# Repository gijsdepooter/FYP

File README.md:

# FYP
Developing a Single Channel Ultrasound Device

This project is being done with the Imperial College London Bioengineering Department, in collaboration with Prof Manos Drakakis and PhD Momen Kamal Tageldeen

This is a Repo for all the relevant material that I am developing/using for a low cost US scanner.

There are a few main parts of the US hardware:

1. The Pulser 
2. The MUX
3. The VGA (voltage gain amplifier)
4. The ADC

**PULSER**

The pulser is responsible for sending high voltage pulses to the piezo transducers in the US probe. I am using the HV7361 from microchip. It takes simple 3 bit digital instructions. These controlls are sent from the raspberry pi pico using the PIO interface to achieve precise timings.

**VGA**

The VGA controlls the amplification of the US signal and corrects for an attenuation of approximately 1dB/MHz/cm in tissue. The TGC profile is set by the MCP4921 DAC, controlled over SPI.
This is a 12 bit DAC that is controlled using the PIO interface of the rapsberry pi pico to achieve the desired speed.

**ADC** 

This project uses the LTC2236, a 10 bit DAC that can sample up to 65Msps. The ADC has a parallel output. The raspberry pi zero is used to decode the parallel ouptut using DMA and the secondary memory interface (SMI). Most of the code that controlls the ADC is from https://github.com/jbentham/rpi, and merely adapted to suit the needs of the IC of choice.

**MUX**

The multiplexer unit is an optional IC to leverage the single channel architecture of this board to controll multiple transducer channels. This allows for constructing B-Mode images with linear and phased arrays.

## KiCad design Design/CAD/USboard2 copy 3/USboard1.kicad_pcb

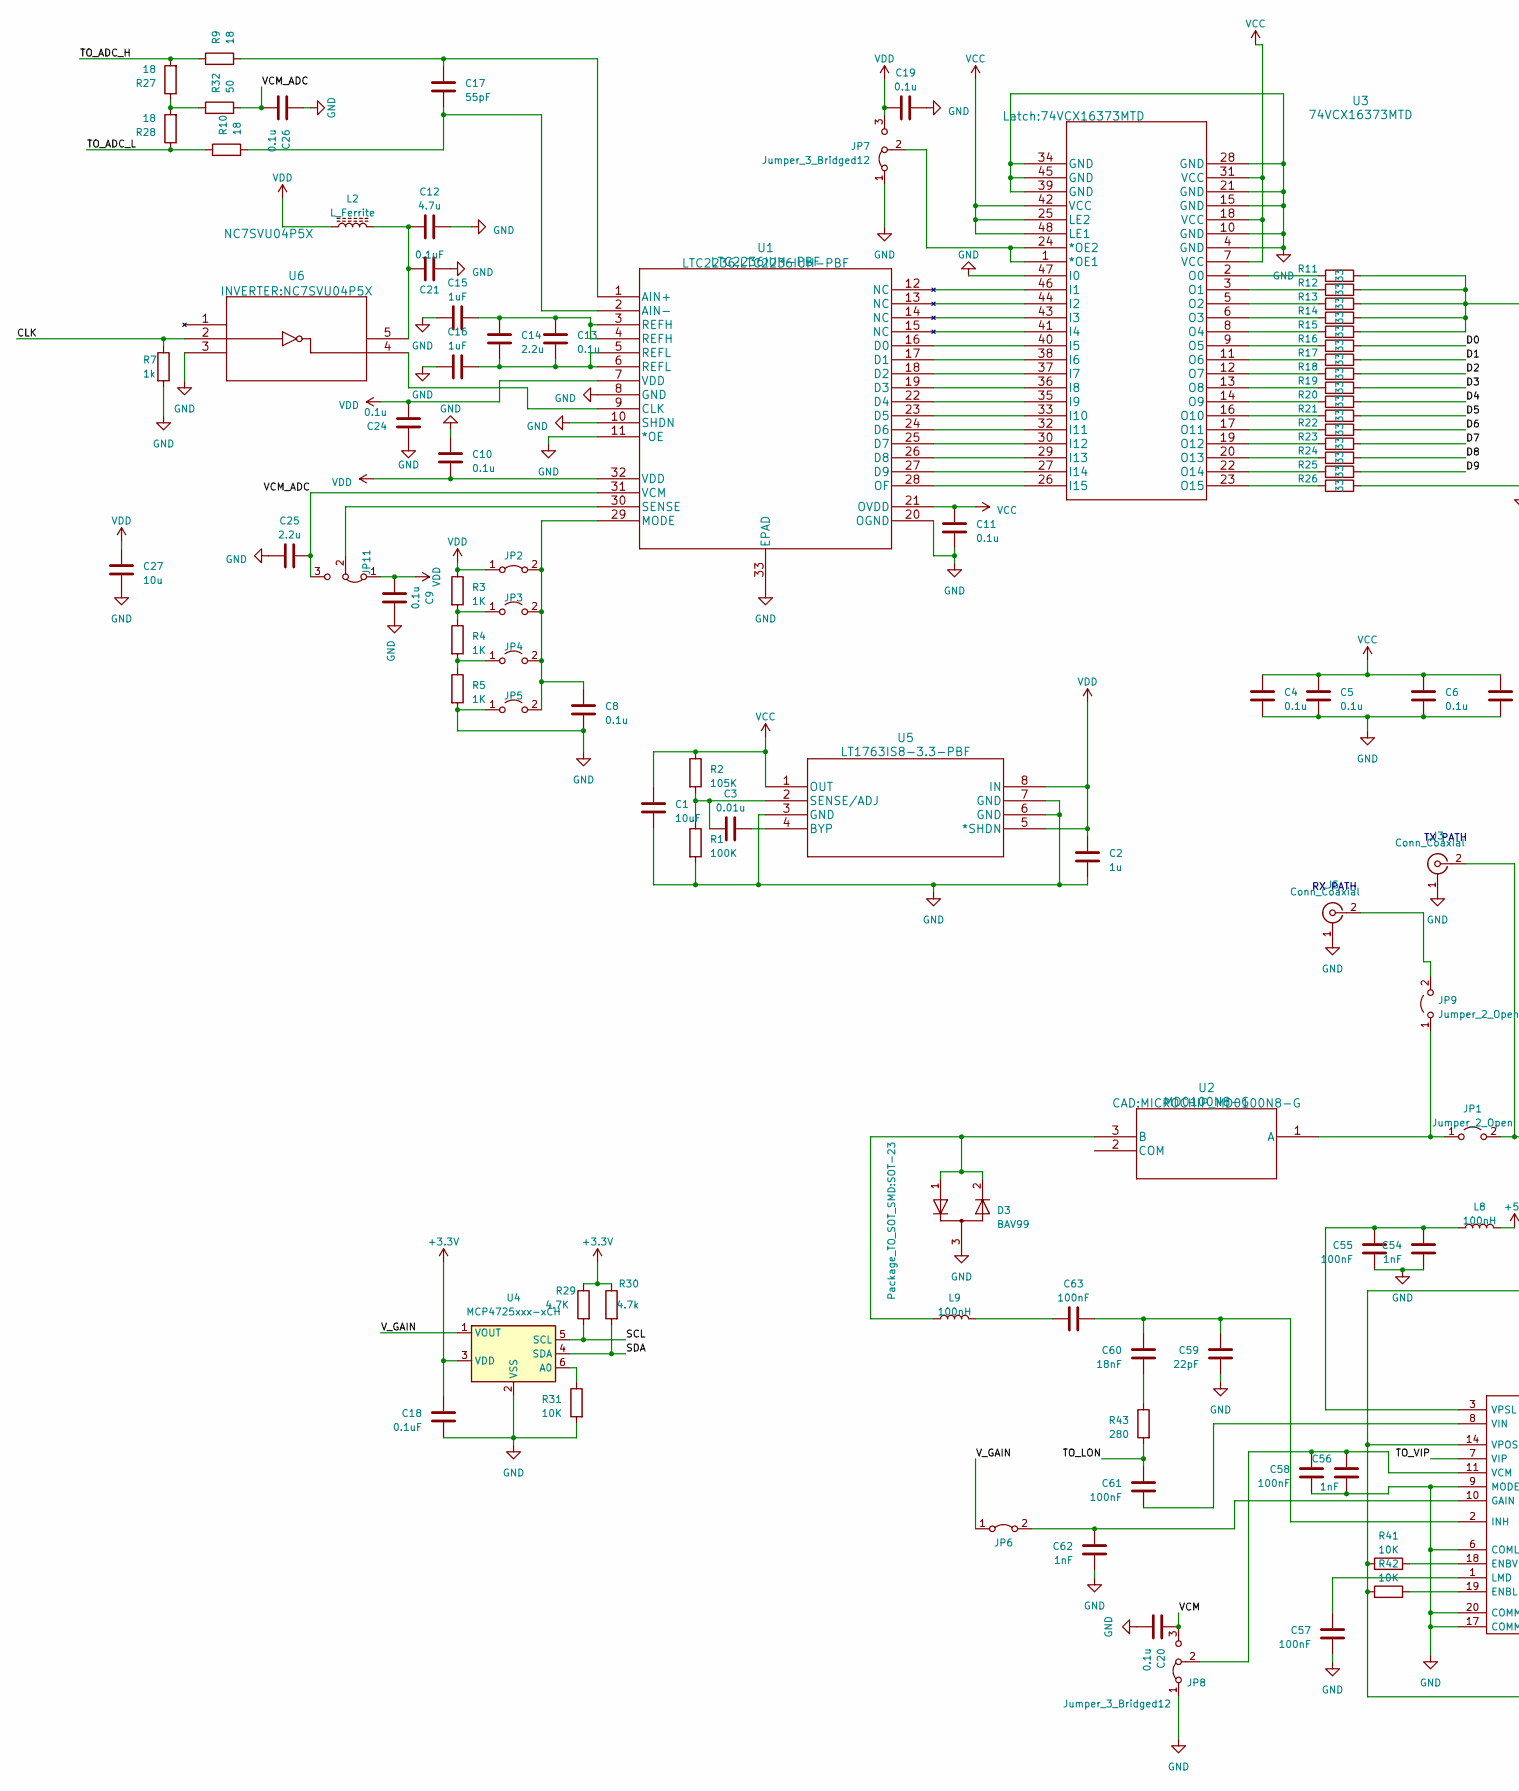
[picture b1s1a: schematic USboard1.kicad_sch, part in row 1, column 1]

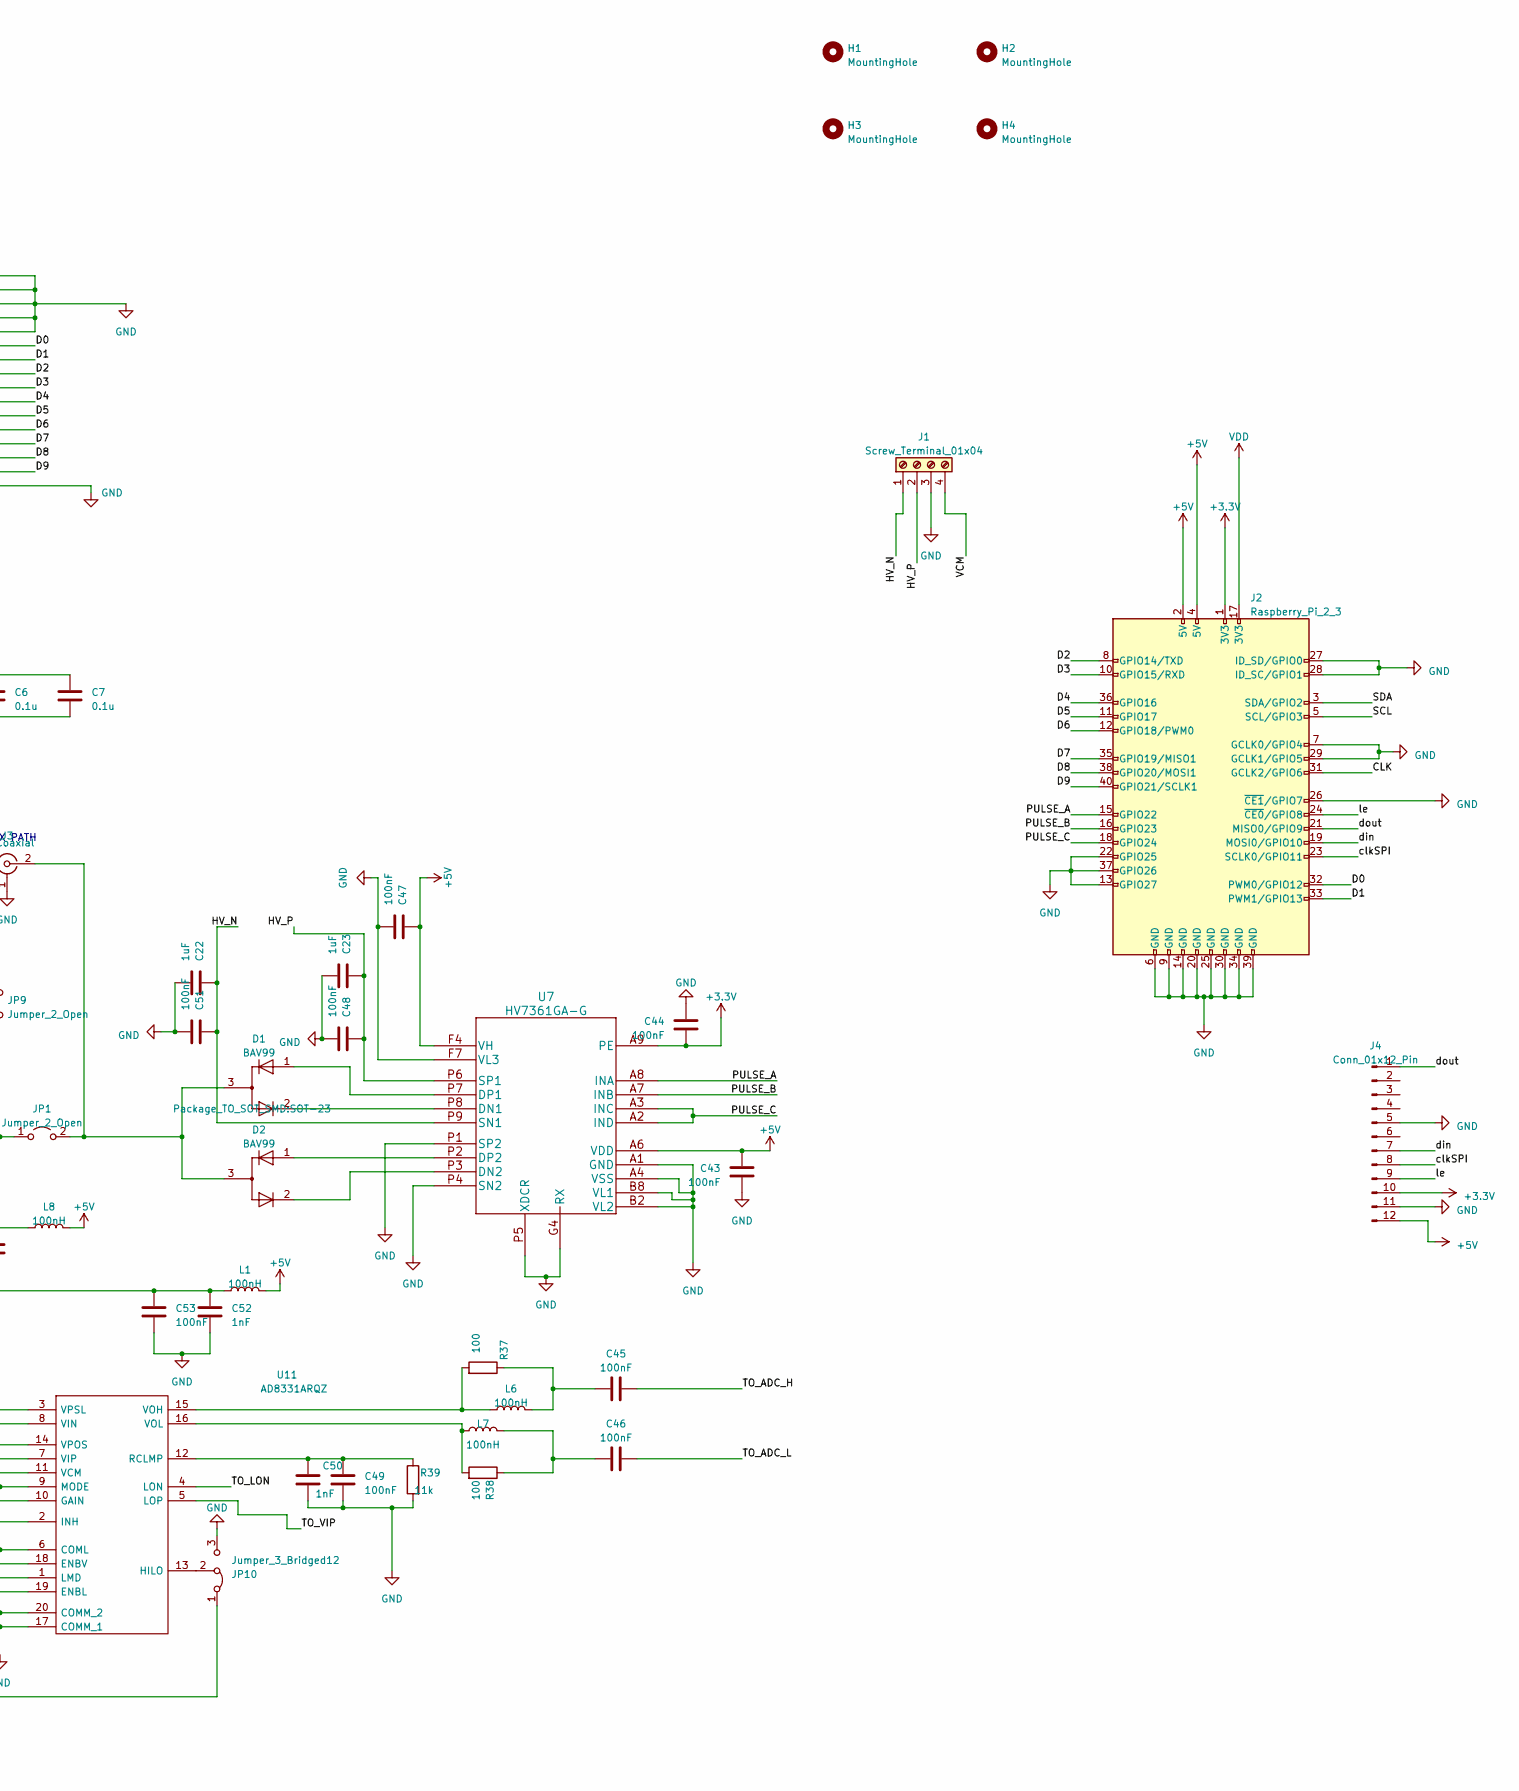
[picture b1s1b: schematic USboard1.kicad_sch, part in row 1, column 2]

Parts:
C1: 10uF; C_0603_1608Metric
C2: 1u; C_0603_1608Metric
C3: 0.01u; C_0603_1608Metric
C4, C5, C6, C7, C8, C9, C10, C11, C13, C19, C20, C24, C26: 0.1u; C_0603_1608Metric
C12: 4.7u; C_0603_1608Metric
C14, C25: 2.2u; C_0603_1608Metric
C15, C16: 1uF; C_0603_1608Metric
C17: 55pF; C_0603_1608Metric
C18, C21: 0.1uF; C_0603_1608Metric
C22, C23: 1uF; C_0805_2012Metric
C27: 10u; C_0603_1608Metric
C43, C44, C45, C46, C47, C48, C49, C51, C53, C55, C57, C58, C61, C63: 100nF; C_0603_1608Metric
C50, C52, C54, C56, C62: 1nF; C_0603_1608Metric
C59: 22pF; C_0603_1608Metric
C60: 18nF; C_0603_1608Metric
D1, D2, D3: BAV99; SOT-23
H1, H2, H3, H4: MountingHole; MountingHole_3.5mm
J1: Screw_Terminal_01x04; 1751264
J2: Raspberry_Pi_2_3; PinSocket_2x20_P2.54mm_Vertical
J3, J5: Conn_Coaxial; RS_526-5785
J4: Conn_01x12_Pin; PinHeader_2x06_P2.54mm_Vertical
JP1, JP3, JP4, JP5, JP9: Jumper_2_Open; PinHeader_2x01_P2.00mm_Vertical
JP2, JP6: Jumper_2_Bridged; PinHeader_2x01_P2.00mm_Vertical
JP7, JP8, JP10, JP11: Jumper_3_Bridged12; PinHeader_1x03_P2.00mm_Vertical
L1, L6, L7, L8, L9: 100nH; L_0603_1608Metric
L2: L_Ferrite; L_0603_1608Metric
R1: 100K; R_0603_1608Metric
R2: 105K; R_0603_1608Metric
R3, R4, R5: 1K; R_0603_1608Metric
R7: 1k; R_0603_1608Metric
R9, R10, R27, R28: 18; R_0603_1608Metric
R11, R12, R13, R14, R15, R16, R17, R18, R19, R20, R21, R22, R23, R24, R25, R26: 33; R_0603_1608Metric
R29: 4.7K; R_0603_1608Metric
R30: 4.7k; R_0603_1608Metric
R31, R41, R42: 10K; R_0603_1608Metric
R32: 50; R_0603_1608Metric
R37, R38: 100; R_0603_1608Metric
R39: 11k; R_0603_1608Metric
R43: 280; R_0603_1608Metric
U1: LTC2236IUH-PBF
U2: MD0100N8-G; MICROCHIP_MD0100N8-G
U3: 74VCX16373MTD
U4: MCP4725xxx-xCH; SOT-23-6
U5: LT1763IS8-3.3-PBF
U6: NC7SVU04P5X
U7: HV7361GA-G
U11: AD8331ARQZ; SOP64P600X175-20N; Manufacturer_Part_Number AD8331ARQZ; Mouser Part Number 584-AD8331ARQZ

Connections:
+3.3V: C18.1, C44.2, J2.1 (3V3), J4.10, R29.1, R30.1, U4.3 (VDD), U7.A9 (PE)
+5V: C43.1, C47.1, J2.2 (5V), J2.4 (5V), J4.12, L1.1, L8.1, U7.A6 (VDD), U7.F4 (VH)
/CLK: J2.31 (GCLK2/GPIO6), R7.1, U6.2 (A)
/D0: J2.32 (PWM0/GPIO12), R16.2
/D1: J2.33 (PWM1/GPIO13), R17.2
/D2: J2.8 (GPIO14/TXD), R18.2
/D3: J2.10 (GPIO15/RXD), R19.2
/D4: J2.36 (GPIO16), R20.2
/D5: J2.11 (GPIO17), R21.2
/D6: J2.12 (GPIO18/PWM0), R22.2
/D7: J2.35 (GPIO19/MISO1), R23.2
/D8: J2.38 (GPIO20/MOSI1), R24.2
/D9: J2.40 (GPIO21/SCLK1), R25.2
/HV_N: C22.1, C51.1, J1.1, U7.P9 (SN1)
/HV_P: C23.1, C48.1, J1.2, U7.P6 (SP1)
/PULSE_A: J2.15 (GPIO22), U7.A8 (INA)
/PULSE_B: J2.16 (GPIO23), U7.A7 (INB)
/PULSE_C: J2.18 (GPIO24), U7.A2 (IND), U7.A3 (INC)
/SCL: J2.5 (SCL/GPIO3), R29.2, U4.5 (SCL)
/SDA: J2.3 (SDA/GPIO2), R30.2, U4.4 (SDA)
/TO_ADC_H: C45.1, R9.1, R27.2
/TO_ADC_L: C46.1, R10.1, R28.1
/TO_LON: C61.1, R43.2, U11.4 (LON)
/TO_VIP: U11.5 (LOP), U11.7 (VIP)
/VCM: C20.1, J1.4, JP8.3 (B)
/VCM_ADC: C25.2, C26.2, JP11.3 (B), R32.2, U1.31 (VCM)
/V_GAIN: JP6.1 (A), U4.1 (VOUT)
/clkSPI: J2.23 (SCLK0/GPIO11), J4.8
/din: J2.19 (MOSI0/GPIO10), J4.7
/dout: J2.21 (MISO0/GPIO9), J4.1
/le: J2.24 (~CE0/GPIO8), J4.9
GND: C1.2, C2.2, C4.2, C5.2, C6.2, C7.2, C8.2, C9.2, C10.1, C11.2, C12.2, C15.2, C16.2, C18.2, C19.2, C20.2, C21.2, C22.2, C23.2, C24.1, C25.1, C26.1, C27.1, C43.2, C44.1, C47.2, C48.2, C49.2, C50.2, C51.2, C52.2, C53.2, C54.2, C55.2, C56.2, C57.2, C58.2, C59.2, C62.2, D3.3 (K), J1.3, J2.6 (GND), J2.7 (GCLK0/GPIO4), J2.9 (GND), J2.13 (GPIO27), J2.14 (GND), J2.20 (GND), J2.22 (GPIO25), J2.25 (GND), J2.26 (~CE1/GPIO7), J2.27 (ID_SD/GPIO0), J2.28 (ID_SC/GPIO1), J2.29 (GCLK1/GPIO5), J2.30 (GND), J2.34 (GND), J2.37 (GPIO26), J2.39 (GND), J3.1 (In), J4.5, J4.11, J5.1 (In), JP5.1 (A), JP7.1 (A), JP8.1 (A), JP10.3 (B), R1.2, R5.2, R7.2, R11.2, R12.2, R13.2, R14.2, R15.2, R26.2, R31.2, R39.2, U1.8 (GND), U1.10 (SHDN), U1.11 (*OE), U1.20 (OGND), U1.33 (EPAD), U3.4 (GND), U3.10 (GND), U3.15 (GND), U3.21 (GND), U3.28 (GND), U3.34 (GND), U3.39 (GND), U3.45 (GND), U3.47 (I0), U4.2 (VSS), U5.3 (GND), U5.6 (GND), U5.7 (GND), U6.3 (GND), U7.A1 (GND), U7.A4 (VSS), U7.B2 (VL2), U7.B8 (VL1), U7.F7 (VL3), U7.G4 (RX), U7.P1 (SP2), U7.P4 (SN2), U7.P5 (XDCR), U11.6 (COML), U11.9 (MODE), U11.17 (COMM_1), U11.20 (COMM_2)
unnamed: C13.1, C14.1, C15.1, U1.3 (REFH), U1.4 (REFH)
unnamed: C13.2, C14.2, C16.1, U1.5 (REFL), U1.6 (REFL)
unnamed: C45.2, L6.1, R37.1
unnamed: C46.2, L7.1, R38.1
unnamed: C60.2, R43.1
unnamed: C63.1, L9.1
unnamed: D1.2 (A), U7.P8 (DN1)
unnamed: D2.2 (A), U7.P3 (DN2)
unnamed: D3.1 (K), D3.2 (A), L9.2, U2.3 (B)
unnamed: D1.3 (K), D2.3 (K), J3.2 (Ext), JP1.2 (B)
unnamed: J5.2 (Ext), JP9.2 (B)
unnamed: JP1.1 (A), JP9.1 (A), U2.1 (A)
unnamed: C8.1, JP2.2 (B), JP3.2 (B), JP4.2 (B), JP5.2 (B), U1.29 (MODE)
unnamed: JP3.1 (A), R3.2, R4.1
unnamed: JP4.1 (A), R4.2, R5.1
unnamed: C62.1, JP6.2 (B), U11.10 (GAIN)
unnamed: JP7.2 (C), U3.1 (*OE1), U3.24 (*OE2)
unnamed: C56.1, C58.1, JP8.2 (C), U11.11 (VCM)
unnamed: C52.1, C53.1, JP10.1 (A), L1.2, R41.2, R42.2, U11.14 (VPOS)
unnamed: JP10.2 (C), U11.13 (HILO)
unnamed: JP11.2 (C), U1.30 (SENSE)
unnamed: R27.1, R28.2, R32.1
unnamed: C17.1, R9.2, U1.1 (AIN+)
unnamed: C17.2, R10.2, U1.2 (AIN-)
unnamed: U1.9 (CLK), U6.4 (Y)
unnamed: U1.16 (D0), U3.40 (I5)
unnamed: U1.17 (D1), U3.38 (I6)
unnamed: U1.18 (D2), U3.37 (I7)
unnamed: U1.19 (D3), U3.36 (I8)
unnamed: U1.22 (D4), U3.35 (I9)
unnamed: U1.23 (D5), U3.33 (I10)
unnamed: U1.24 (D6), U3.32 (I11)
unnamed: U1.25 (D7), U3.30 (I12)
unnamed: U1.26 (D8), U3.29 (I13)
unnamed: U1.27 (D9), U3.27 (I14)
unnamed: U1.28 (OF), U3.26 (I15)
unnamed: R11.1, U3.2 (O0)
unnamed: R12.1, U3.3 (O1)
unnamed: R13.1, U3.5 (O2)
unnamed: R14.1, U3.6 (O3)
unnamed: R15.1, U3.8 (O4)
unnamed: R16.1, U3.9 (O5)
unnamed: R17.1, U3.11 (O6)
unnamed: R18.1, U3.12 (O7)
unnamed: R19.1, U3.13 (O8)
unnamed: R20.1, U3.14 (O9)
unnamed: R21.1, U3.16 (O10)
unnamed: R22.1, U3.17 (O11)
unnamed: R23.1, U3.19 (O12)
unnamed: R24.1, U3.20 (O13)
unnamed: R25.1, U3.22 (O14)
unnamed: R26.1, U3.23 (O15)
unnamed: R31.1, U4.6 (A0)
unnamed: C3.2, U5.4 (BYP)
unnamed: C3.1, R1.1, R2.2, U5.2 (SENSE/ADJ)
unnamed: C12.1, C21.1, L2.2, U6.5 (VCC)
unnamed: D1.1 (K), U7.P7 (DP1)
unnamed: D2.1 (K), U7.P2 (DP2)
unnamed: R42.1, U11.19 (ENBL)
unnamed: R41.1, U11.18 (ENBV)
unnamed: C59.1, C60.1, C63.2, U11.2 (INH)
unnamed: C57.1, U11.1 (LMD)
unnamed: C49.1, C50.1, R39.1, U11.12 (RCLMP)
unnamed: C61.2, U11.8 (VIN)
unnamed: L6.2, R37.2, U11.15 (VOH)
unnamed: L7.2, R38.2, U11.16 (VOL)
unnamed: C54.1, C55.1, L8.2, U11.3 (VPSL)
VCC: C1.1, C4.1, C5.1, C6.1, C7.1, C11.1, R2.1, U1.21 (OVDD), U3.7 (VCC), U3.18 (VCC), U3.25 (LE2), U3.31 (VCC), U3.42 (VCC), U3.48 (LE1), U5.1 (OUT)
VDD: C2.1, C9.1, C10.2, C19.1, C24.2, C27.2, J2.17 (3V3), JP2.1 (A), JP7.3 (B), JP11.1 (A), L2.1, R3.1, U1.7 (VDD), U1.32 (VDD), U5.5 (*SHDN), U5.8 (IN)

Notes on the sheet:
TX PATH
RX PATH

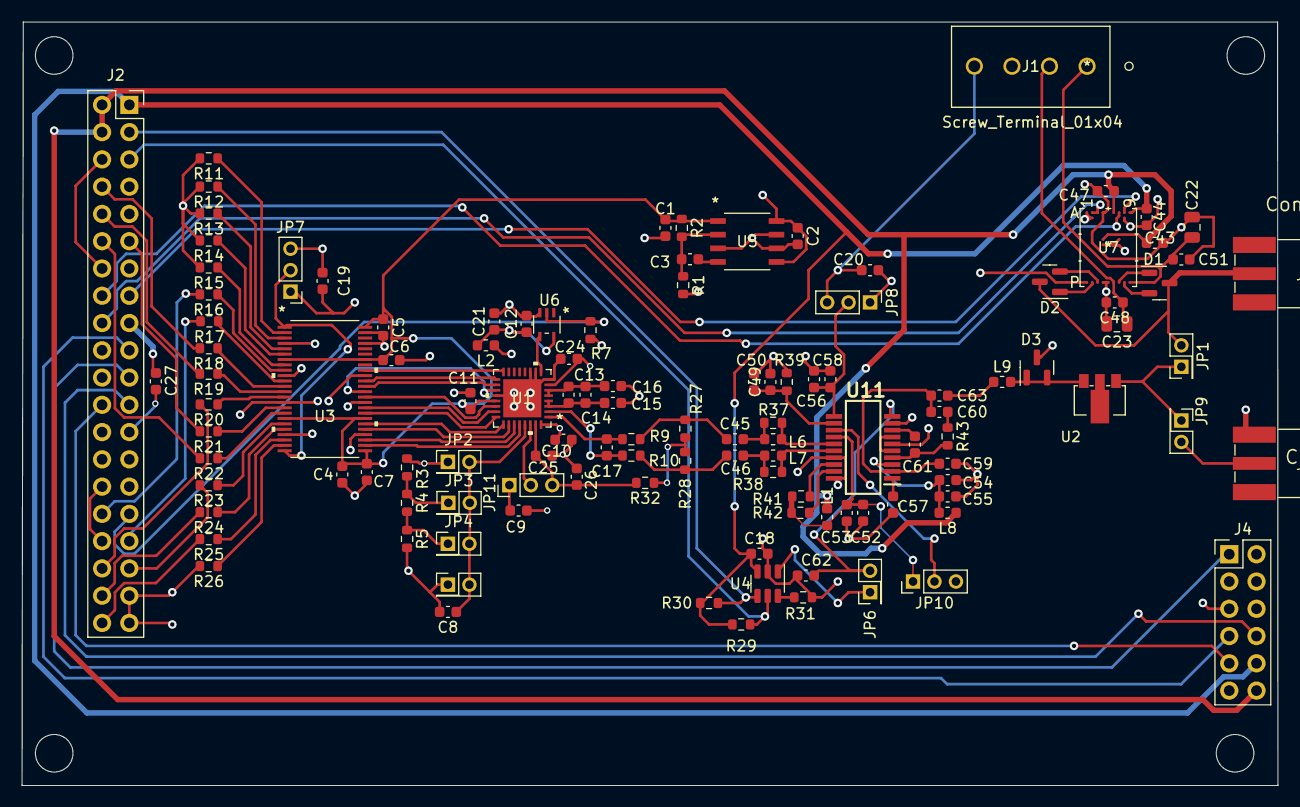
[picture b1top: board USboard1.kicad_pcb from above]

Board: 4 copper layers, 117.0 x 71.1 mm, 121 parts (0 on the bottom side), 101 nets.

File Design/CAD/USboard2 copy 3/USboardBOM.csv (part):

Source:,/Users/gijsdepooter/Desktop/UROP/CAD/USboard2 copy 2/USboard1.kicad_sch,,,,,,,,,,,,,,,
Date:,"Wednesday, 22 March 2023 at 10:44:08",,,,,,,,,,,,,,,
Tool:,Eeschema (7.0.0-0),,,,,,,,,,,,,,,
Generator:,/Applications/KiCad/KiCad.app/Contents/SharedSupport/plugins/bom_csv_grouped_by_value_with_fp.py,,,,,,,,,,,,,,,
Component Count:,,,,,,,,,,,,,,,,
Ref,Qnty,Value,Cmp name,Footprint,Description,SUPPLIER,Supplier Part Number,Manufacturer,Manufacturer Part Number,Link,,,,,https://www.mouser.co.uk/ProductDetail/KYOCERA-AVX/0603ZD106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,
"C1, C27",2,10uF,C,Capacitor_SMD:C_0603_1608Metric,Unpolarized capacitor,Mouser,581-0603ZD106KAT2A,KYOCERA AVX,0603ZD106KAT2A,,,,,,https://www.mouser.co.uk/ProductDetail/TAIYO-YUDEN/HMJ212DC7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,
"C22, C23",2,1uF 100VDC,C,Capacitor_SMD:C_0805_2012Metric,Unpolarized capacitor,Mouser,963-MJ212DC7105KGHTE,TAIYO YUDEN,HMJ212DC7105KGHTE,,,,,,https://www.mouser.co.uk/ProductDetail/TDK/C0603X5R1A103K030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,
C3,1,0.01uF,C,Capacitor_SMD:C_0603_1608Metric,Unpolarized capacitor,Mouser,581-06035C103KAT4A,KYOCERA AVX,06035C103KAT4A,,,,,,https://www.mouser.co.uk/ProductDetail/KEMET/C0603C104K8RAC?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,
C59,1,22pF,C,Capacitor_SMD:C_0603_1608Metric,Unpolarized capacitor,Mouser,603-CC603FRNPO9BN220,YAGEO,CC0603FRNPO9BN220,,,,,,,
"C4, C5, C6, C7, C8, C9, C10, C11, C13,C18, C19, C20, C21,  C24, C26, C43, C44, C45, C46, C47, C49, C53, C55, C57, C58, C61, C63",29,0.1uF 10VDC 10%,C,Capacitor_SMD:C_0603_1608Metric,Unpolarized capacitor,Mouser,80-C0603C104K8RAC,KEMET,C0603C104K8RAC,,,,,,https://www.mouser.co.uk/ProductDetail/KEMET/C0603C475K8PACT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,
C12,1,4.7uF,C,Capacitor_SMD:C_0603_1608Metric,Unpolarized capacitor,Mouser,791-0603X475K100CT,WALSIN,0603X475K100CT,,,,,,https://www.mouser.co.uk/ProductDetail/KEMET/C0603C225K8RAC7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,
"C14, C25",2,2.2uF,C,Capacitor_SMD:C_0603_1608Metric,Unpolarized capacitor,Mouser,80-C0603C225K8R7411,KEMET,C0603C225K8RAC7411,,,,,,https://www.mouser.co.uk/ProductDetail/TDK/C1608X7R1A105K080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,
"C2, C15, C16",3,1uF 10VDC 10%,C,Capacitor_SMD:C_0603_1608Metric,Unpolarized capacitor,Mouser,810-C1608X7R1A105K,TDK,C1608X7R1A105K080AC,,,,,,https://www.mouser.co.uk/ProductDetail/KEMET/C0603C560J8HACT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,
C17,1,56pF,C,Capacitor_SMD:C_0603_1608Metric,Unpolarized capacitor,Mouser,80-C0603C560J8HACTU,KEMET,C0603C560J8HACTU,,,,,,https://www.mouser.co.uk/ProductDetail/KEMET/C0603C102K8RACA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,
"C50, C52, C54, C56, C62",5,1nF,C,Capacitor_SMD:C_0603_1608Metric,Unpolarized capacitor,Mouser,80-C0603C102K8RAUTO,KEMET,C0603C102K8RACAUTO,,,,,,https://www.mouser.co.uk/ProductDetail/TAIYO-YUDEN/HMJ107BB7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,
"C48, C51",2,100nF 100VDC,C,Capacitor_SMD:C_0603_1608Metric,Unpolarized capacitor,Mouser,963-HMJ107BB7104KAHT,TAIYO YUDEN,HMJ107BB7104KAHT,,,,,,https://www.mouser.co.uk/ProductDetail/TAIYO-YUDEN/LMK107SD1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,
C60,1,18nF,C,Capacitor_SMD:C_0603_1608Metric,Unpolarized capacitor,Mouser,80-C0603C183K4R,KEMET,C0603C183K4RACTU,,,,,,https://uk.farnell.com/diodes-inc/bav99/diode-ss-dual-100v-0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,
"D1, D2, D3",3,BAV99,BAV99,Package_TO_SOT_SMD:SOT-23,"BAV99 High-speed switching diodes, SOT-23",Farnell,1902422,DIODES INC,BAV99,,,,,,https://www.digikey.co.uk/en/products/detail/phoenix-contact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,
J1,1,Screw_Terminal_01x04,Screw_Terminal_01x04,screwConn3:1751264,TERM BLK 4POS SIDE ENT 3.5MM PCB,Digikey,277-5744-ND,Pheonix Contact,1751264,,,,,,https://www.mouser.co.uk/ProductDetail/Adafruit/2222?qs=GURa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,
J2,1,Raspberry_Pi_2_3,Raspberry_Pi_2_3,Connector_PinSocket_2.54mm:PinSocket_2x20_P2.54mm_Vertical,expansion header for Raspberry Pi 2 & 3,Mouser,485-2222,Adafruit,2222,,,,,,https://uk.rs-online.com/web/p/coaxial-connectors/5265785?cm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,
"J3, J5",2,Conn_Coaxial,Conn_Coaxial,Connector_Coaxial:SMA_Amphenol_132289_EdgeMount,coaxial connector SMA,RS,526-5785,,526-5785,,,,,,https://www.mouser.co.uk/ProductDetail/Amphenol-FCI/10129381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,
J4,1,Conn_01x12_Pin,Conn_01x12_Pin,Connector_PinHeader_2.54mm:PinHeader_2x06_P2.54mm_Vertical,"Generic connector, single row, 02x6",Mouser,649-1012938191203BLF,Amphenol FCI,10129381-912003BLF,,,,,,https://www.mouser.co.uk/ProductDetail/Harwin/M22-2510205?qs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,
"JP1, JP3, JP4, JP5, JP9",5,Jumper_2_Open,Jumper_2_Open,Connector_PinHeader_2.00mm:PinHeader_2x01_P2.00mm_Vertical,Headers & Wire Housings 2 PIN SIL VERTICAL GOLD PIN HEADER,Mouser,855-M22-2510205,Harwin,M22-2510205,,,,,,https://www.mouser.co.uk/ProductDetail/Harwin/M22-2510205?qs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,
"JP2, JP6",2,Jumper_2_Bridged,Jumper_2_Bridged,Connector_PinHeader_2.00mm:PinHeader_2x01_P2.00mm_Vertical,Headers & Wire Housings 2 PIN SIL VERTICAL GOLD PIN HEADER,Mouser,855-M22-2510205,Harwin,M22-2510205,,,,,,https://www.mouser.co.uk/ProductDetail/TE-Connectivity/23551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,
L2,1,Ferrite,L,Inductor_SMD:L_0603_1608Metric,Ferrite bead,Farnell,BLM18B,Murata Electronics,BLM18BB470SN1D,,,,,,,
"JP7, JP8, JP10, JP11",4,Jumper_3_Bridged12,Jumper_3_Bridged12,Connector_PinHeader_2.00mm:PinHeader_1x03_P2.00mm_Vertical,"Jumper, 3-pole, pins 1+2 closed/bridged",Mouser,571-2355182-3,TE Connectivity,2355182-3,,,,,,https://www.mouser.co.uk/ProductDetail/Murata-Electronics/BL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,
"L1, L6, L7, L8, L9",5,100nH,L,Inductor_SMD:L_0603_1608Metric,Inductor,Mouser,81-BLM18BA750SN1D,Murata Electronics,BLM18BA750SN1D,,,,,,https://www.mouser.co.uk/ProductDetail/YAGEO/RC0603FR-07100K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,
R1,1,100K,R,Resistor_SMD:R_0603_1608Metric,Resistor,Mouser,603-RC0603FR-07100KL,YAGEO,RC0603FR-07100KL,,,,,,https://www.mouser.co.uk/ProductDetail/YAGEO/RT0603DRE07105K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,
R2,1,105K,R,Resistor_SMD:R_0603_1608Metric,Resistor,Mouser,603-RT0603DRE07105KL,YAGEO,RT0603DRE07105KL,,,,,,https://www.mouser.co.uk/ProductDetail/YAGEO/RP0603BRD071KL?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,
"R3, R4, R5, R7",4,1K,R,Resistor_SMD:R_0603_1608Metric,Resistor,Mouser,603-RP0603BRD071KL,YAGEO,RP0603BRD071KL,,,,,,https://www.mouser.co.uk/ProductDetail/EPCOS-TDK/B82496C3101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,
"R9, R10, R27, R28",4,18,R,Resistor_SMD:R_0603_1608Metric,Resistor,Mouser,603-RC0603FR-0718RL,YAGEO,RC0603FR-0718RL,,,,,,https://www.mouser.co.uk/ProductDetail/YAGEO/RC0603FR-0733RL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,
R32,1,49.9,R,Resistor_SMD:R_0603_1608Metric,Resistor,Mouser,667-ERJ-PA3F49R9V,Panasonic,ERJ-PA3F49R9V,,,,,,https://www.mouser.co.uk/ProductDetail/YAGEO/RC0603FR-0718RL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,
"R11, R12, R13, R14, R15, R16, R17, R18, R19, R20, R21, R22, R23, R24, R25, R26",16,33,R,Resistor_SMD:R_0603_1608Metric,Resistor,Mouser,71-CRCW060333R0FKEAH,vISHAY / Dale,CRCW060333R0FKEAHP,,,,,,https://www.mouser.co.uk/ProductDetail/Vishay-Dale/CRCW06034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,
"R29, R30",2,4.7K,R,Resistor_SMD:R_0603_1608Metric,Resistor,Mouser,71-CRCW0603-4.7K,Vishay / Draloric,CRCW06034K70FKTA,,,,,,https://www.mouser.co.uk/ProductDetail/YAGEO/RC0603FR-0710KL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,
"R31, R41, R42, ",3,10K,R,Resistor_SMD:R_0603_1608Metric,Resistor,Mouser,603-RC0603FR-0710KL,YAGEO,RC0603FR-0710KL,,,,,,https://www.mouser.co.uk/ProductDetail/Bourns/CR0603-FX-1000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,
"R37, R38",2,100,R,Resistor_SMD:R_0603_1608Metric,Resistor,Mouser,652-CR0603FX-1000ELF,Bourns,CR0603-FX-1000ELF,,,,,,https://www.mouser.co.uk/ProductDetail/YAGEO/AC0603FR-0711KL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,
R39,1,11k,R,Resistor_SMD:R_0603_1608Metric,Resistor,Mouser,603-AC0603FR-0711KL,YAGEO,AC0603FR-0711KL,,,,,,https://www.mouser.co.uk/ProductDetail/YAGEO/AC0603FR-07280R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,
R43,1,280,R,Resistor_SMD:R_0603_1608Metric,Resistor,Mouser,603-AC0603FR-07280RL,YAGEO,AC0603FR-07280RL,,,,,,https://www.mouser.co.uk/ProductDetail/Microchip-Technology-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,
U2,1,MD0100N8-G,MD0100N8-G,MDO100:MD0100N8-G,T/R protection switch,Mouser,689-MD0100N8-G,Microchip,MD0100N8-G,,,,,,https://www.mouser.co.uk/ProductDetail/Microchip-Technology/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,
U4,1,MCP4725A3T-E/CH,MCP4725A3T-E/CH,Package_TO_SOT_SMD:SOT-23-6,"12-bit Digital-to-Analog Converter, integrated EEPROM, I2C interface, SOT-23-6",Mouser,579-MCP4725A3T-E/CH,Microchip,MCP4725A3T-E/CH,,,,,,https://www.mouser.co.uk/ProductDetail/Analog-Devices/LT1763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,
U5,1,LT1763IS8-3.3-PBF,LT1763IS8-3.3-PBF,VCCsup:LT1763IS8-3.3-PBF,Voltage regulator,Mouser,584-LT1763IS8-3.3PBF,Analog Devices,LT1763IS8-3.3#PBF,,,,,,https://dk.farnell.com/en-DK/on-semiconductor/nc7svu04p5x/in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,
U6,1,SN74AUP1G14DCKT,SN74AUP1G14DCKT,INVERTER:NC7SVU04P5X,Inverter,Farnell,595-SN74AUP1G14DCKT,TI,SN74AUP1G14DCKT,,,,,,,
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
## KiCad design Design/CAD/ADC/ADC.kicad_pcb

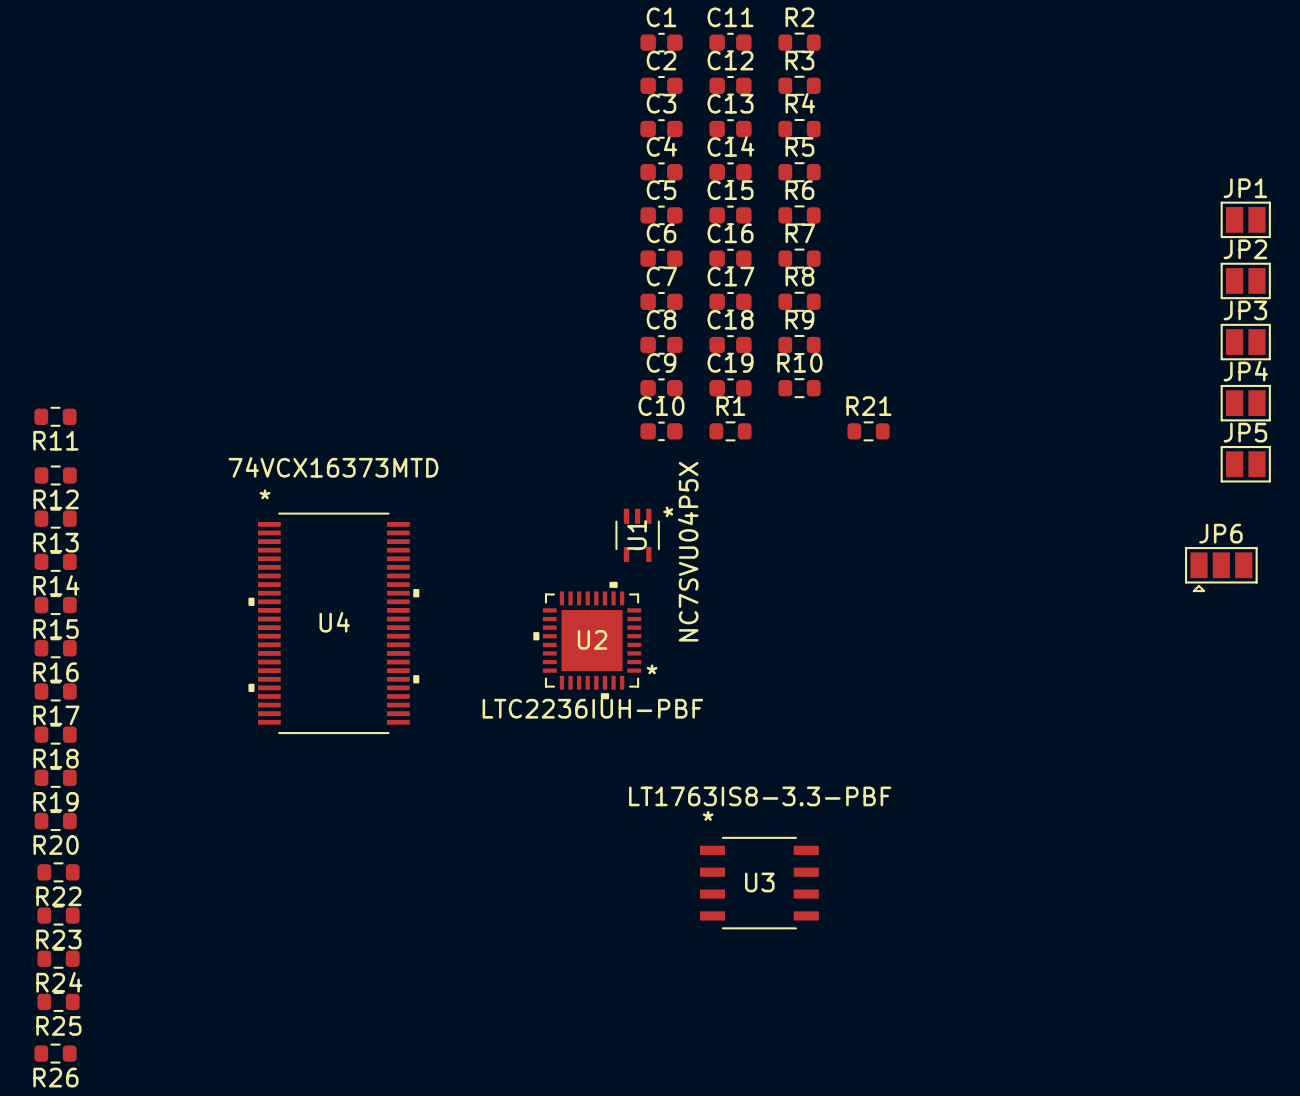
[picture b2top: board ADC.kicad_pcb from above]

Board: 2 copper layers, 55 parts (0 on the bottom side), 44 nets, no tracks yet.

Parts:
C1, C2, C5, C9, C10, C13, C14, C16, C17, C18, C19: 0.1u; C_0603_1608Metric
C3: 4.7u; C_0603_1608Metric
C4: 0.2n; C_0603_1608Metric
C6, C7, C15: 1u; C_0603_1608Metric
C8: 2.2u; C_0603_1608Metric
C11: 10uF; C_0603_1608Metric
C12: 0.01u; C_0603_1608Metric
JP1, JP2: Jumper_2_Bridged; SolderJumper-2_P1.3mm_Open_Pad1.0x1.5mm
JP3, JP4, JP5: Jumper_2_Open; SolderJumper-2_P1.3mm_Open_Pad1.0x1.5mm
JP6: Jumper_3_Bridged12; SolderJumper-3_P1.3mm_Open_Pad1.0x1.5mm
R1: 49.9; R_0603_1608Metric
R2, R3: 1k; R_0603_1608Metric
R4, R5: 18; R_0603_1608Metric
R6, R7, R8: 1K; R_0603_1608Metric
R9: 105K; R_0603_1608Metric
R10: 100K; R_0603_1608Metric
R11, R12, R13, R14, R15, R16, R17, R18, R19, R20, R21, R22, R23, R24, R25, R26: 33; R_0603_1608Metric
U1: NC7SVU04P5X
U2: LTC2236IUH-PBF
U3: LT1763IS8-3.3-PBF
U4: 74VCX16373MTD

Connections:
/CLK: R1.1, R2.1, R3.2, U1.2 (A)
GND: C1.2, C2.1, C3.2, C5.1, C6.2, C7.2, C10.2, C11.2, C13.2, C14.2, C15.2, C16.2, C17.2, C18.2, C19.2, JP5.1 (A), R1.2, R2.2, R8.2, R10.2, R11.2, R12.2, R13.2, R14.2, R15.2, R26.2, U1.3 (GND), U2.8 (GND), U2.10 (SHDN), U2.11 (*OE), U2.20 (OGND), U2.31 (VCM), U2.33 (EPAD), U3.3 (GND), U3.6 (GND), U3.7 (GND), U4.4 (GND), U4.10 (GND), U4.15 (GND), U4.21 (GND), U4.28 (GND), U4.34 (GND), U4.39 (GND), U4.45 (GND), U4.47 (I0)
unnamed: C6.1, C8.1, C9.1, U2.3 (REFH), U2.4 (REFH)
unnamed: C7.1, C8.2, C9.2, U2.5 (REFL), U2.6 (REFL)
unnamed: C1.1, JP1.2 (B), U2.30 (SENSE)
unnamed: C10.1, JP2.2 (B), JP3.2 (B), JP4.2 (B), JP5.2 (B), U2.29 (MODE)
unnamed: JP3.1 (A), R6.2, R7.1
unnamed: JP4.1 (A), R7.2, R8.1
unnamed: C13.1, JP6.1 (A)
unnamed: JP6.2 (C), U4.1 (*OE1), U4.24 (*OE2)
unnamed: U1.4 (Y), U2.9 (CLK)
unnamed: C4.1, R4.2, U2.1 (AIN+)
unnamed: C4.2, R5.2, U2.2 (AIN-)
unnamed: U2.16 (D0), U4.40 (I5)
unnamed: U2.17 (D1), U4.38 (I6)
unnamed: U2.18 (D2), U4.37 (I7)
unnamed: U2.19 (D3), U4.36 (I8)
unnamed: U2.22 (D4), U4.35 (I9)
unnamed: U2.23 (D5), U4.33 (I10)
unnamed: U2.24 (D6), U4.32 (I11)
unnamed: U2.25 (D7), U4.30 (I12)
unnamed: U2.26 (D8), U4.29 (I13)
unnamed: U2.27 (D9), U4.27 (I14)
unnamed: U2.28 (OF), U4.26 (I15)
unnamed: C12.2, U3.4 (BYP)
unnamed: C12.1, R9.2, R10.1, U3.2 (SENSE/ADJ)
unnamed: R11.1, U4.2 (O0)
unnamed: R12.1, U4.3 (O1)
unnamed: R13.1, U4.5 (O2)
unnamed: R14.1, U4.6 (O3)
unnamed: R15.1, U4.8 (O4)
unnamed: R16.1, U4.9 (O5)
unnamed: R17.1, U4.11 (O6)
unnamed: R18.1, U4.12 (O7)
unnamed: R19.1, U4.13 (O8)
unnamed: R20.1, U4.14 (O9)
unnamed: R21.1, U4.16 (O10)
unnamed: R22.1, U4.17 (O11)
unnamed: R23.1, U4.19 (O12)
unnamed: R24.1, U4.20 (O13)
unnamed: R25.1, U4.22 (O14)
unnamed: R26.1, U4.23 (O15)
VCC: C11.1, C14.1, C16.1, C17.1, C18.1, C19.1, R9.1, U2.21 (OVDD), U3.1 (OUT), U4.7 (VCC), U4.18 (VCC), U4.25 (LE2), U4.31 (VCC), U4.42 (VCC), U4.48 (LE1)
VDD: C2.2, C3.1, C5.2, C15.1, JP1.1 (A), JP2.1 (A), JP6.3 (B), R3.1, R6.1, U1.5 (VCC), U2.7 (VDD), U2.32 (VDD), U3.5 (*SHDN), U3.8 (IN)

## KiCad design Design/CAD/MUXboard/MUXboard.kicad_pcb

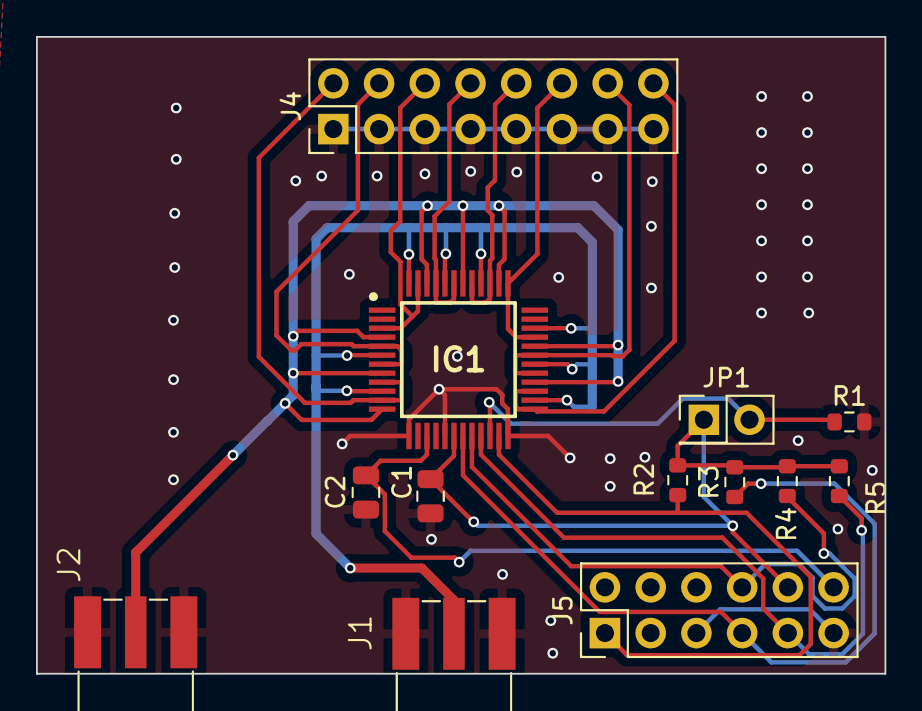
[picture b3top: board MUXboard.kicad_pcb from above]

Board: 2 copper layers, 47.1 x 35.4 mm, 13 parts (0 on the bottom side), 18 nets.

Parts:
C1, C2: 1u; C_0805_2012Metric
IC1: HV2607T-C_R8X; QFP50P900X900X160-48N
J1, J2: Conn_Coaxial; RS_526-5785
J4: Conn_01x16_Pin; PinHeader_2x08_P2.54mm_Vertical
J5: Conn_01x12_Pin; PinHeader_2x06_P2.54mm_Vertical
JP1: Jumper_2_Open; PinHeader_2x01_P2.54mm_Vertical
R1, R2, R3, R4, R5: 10K; R_0603_1608Metric

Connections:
+3.3V: C1.1, IC1.18 (VLL), J5.10, JP1.1 (A), R2.2, R3.2, R4.2, R5.2
+5V: C2.1, IC1.15 (VDD), J5.12
/RX: IC1.4 (SW4A), IC1.8 (SW2A), IC1.12 (SW0A), IC1.28 (SW14A), IC1.32 (SW12A), IC1.38 (SW10A), IC1.42 (SW8A), IC1.46 (SW6A), J2.2 (Ext)
/TX: IC1.6 (SW3A), IC1.10 (SW1A), IC1.26 (SW15A), IC1.30 (SW13A), IC1.34 (SW11A), IC1.40 (SW9A), IC1.44 (SW7A), IC1.48 (SW5A), J1.2 (Ext)
/clk: IC1.20 (CLK), J5.8, R4.1
/clr: IC1.22 (CLR), JP1.2 (B), R1.1
/din: IC1.19 (DIN), J5.7, R3.1
/dout: IC1.23 (DOUT), J5.1, R2.1
/le: IC1.21 (~LE), J5.9, R5.1
/tr1: IC1.9 (SW1B), IC1.11 (SW0B), J4.2
/tr2: IC1.5 (SW3B), IC1.7 (SW2B), J4.4 (Pin_2)
/tr3: IC1.3 (SW4B), IC1.47 (SW5B), J4.6 (Pin_3)
/tr4: IC1.43 (SW7B), IC1.45 (SW6B), J4.8 (Pin_4)
/tr5: IC1.39 (SW9B), IC1.41 (SW8B), J4.10 (Pin_5)
/tr6: IC1.33 (SW11B), IC1.37 (SW10B), J4.12 (Pin_6)
/tr7: IC1.29 (SW13B), IC1.31 (SW12B), J4.14 (Pin_7)
/tr8: IC1.25 (SW15B), IC1.27 (SW14B), J4.16 (Pin_8)
GND: C1.2, C2.2, IC1.13 (GND), IC1.17 (DGND), IC1.24 (NC/RGND), J1.3, J1.4, J1.5, J2.3, J2.4, J2.5, J4.1 (Pin_9), J4.3 (Pin_10), J4.5 (Pin_11), J4.7 (Pin_12), J4.9 (Pin_13), J4.11 (Pin_14), J4.13 (Pin_15), J4.15 (Pin_16), J5.5, J5.11, R1.2

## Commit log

2022-12-07 Created using Colaboratory
2023-05-31 Mian project firmware
2023-06-01 results and worklog
2023-06-01 remove_unpacked image
2023-06-01 change of dirs
2023-06-09 new results
2023-06-11 new reuslts
2023-06-12 new images

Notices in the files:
parts and their libraries:
Copyright 2021 Accelerated Designs. All rights reserved.
